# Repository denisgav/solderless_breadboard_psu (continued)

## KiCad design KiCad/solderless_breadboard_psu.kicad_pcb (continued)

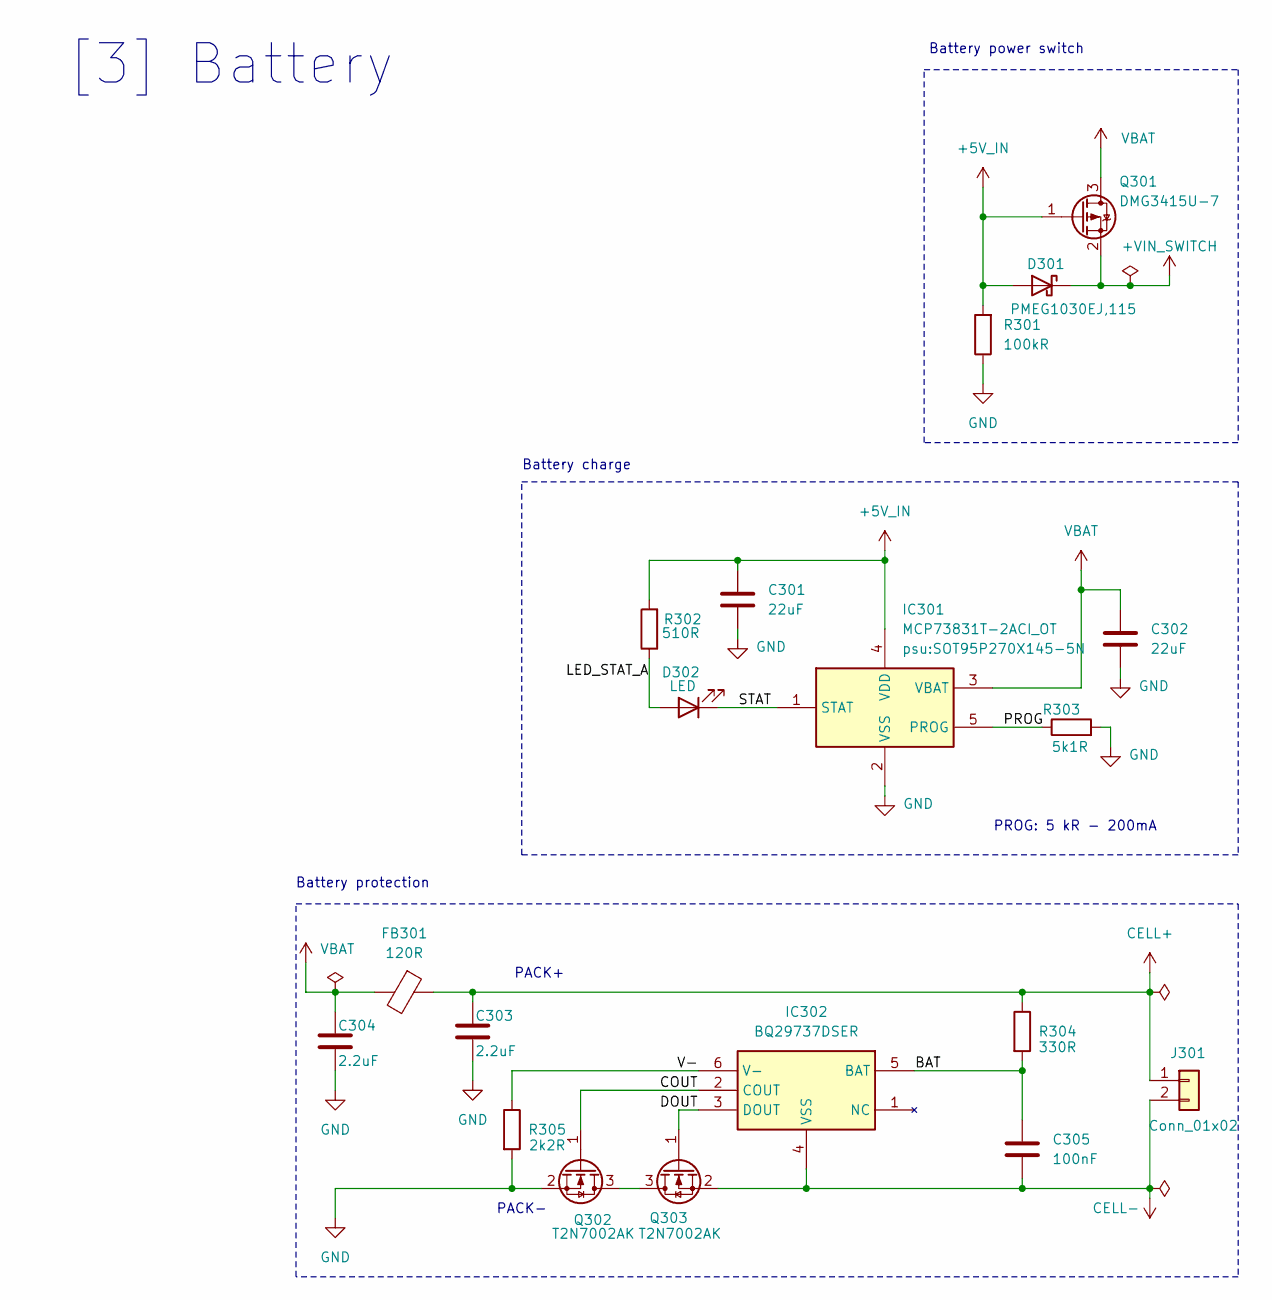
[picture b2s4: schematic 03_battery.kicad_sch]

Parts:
C301, C302: 22uF; C_0603_1608Metric; Manufacturer Part Number CL10A226MP8NUNE
C303, C304: 2.2uF; C_0603_1608Metric; Manufacturer Part Number CL10A225KO8NNNC
C305: 100nF; C_0402_1005Metric; Manufacturer Part Number CL05B104KO5NNNC
D301: PMEG1030EJ,115; D_SOD-323F; Manufacturer Part Number PMEG1030EJ,115
D302: LED; LED_0603_1608Metric; Manufacturer Part Number XL-1608SURC-06
FB301: 120R; Fuse_0603_1608Metric; Manufacturer Part Number BLM18PG121SN1D
IC301: MCP73831T-2ACI_OT; SOT95P270X145-5N; Manufacturer Part Number MCP73831T-2ACI/OT
IC302: BQ29737DSER; SON50P150X150X80-6N; Manufacturer Part Number BQ29737DSER
J301: Conn_01x02; PinHeader_1x02_P2.54mm_Vertical
Q301: DMG3415U-7; SOT-23; Manufacturer Part Number DMG3415U-7
Q302, Q303: T2N7002AK; SOT-23; Manufacturer Part Number T2N7002AK,LM
R301: 100kR; R_0402_1005Metric; Manufacturer Part Number 0402WGF1003TCE
R302: 510R; R_0402_1005Metric; Manufacturer Part Number 0402WGF5100TCE
R303: 5k1R; R_0402_1005Metric; Manufacturer Part Number 0402WGF5101TCE
R304: 330R; R_0402_1005Metric; Manufacturer Part Number 0402WGF3300TCE
R305: 2k2R; R_0402_1005Metric; Manufacturer Part Number 0402WGF2201TCE

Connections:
+5V_IN: C301.1, D301.2 (A), IC301.4 (VDD), Q301.1 (G), R301.2, R302.2; also elsewhere on the board
+VIN_SWITCH: D301.1 (K), Q301.2 (S); also elsewhere on the board
/[3] Battery/BAT: C305.1, IC302.5 (BAT), R304.2
/[3] Battery/COUT: IC302.2 (COUT), Q302.1 (G)
/[3] Battery/DOUT: IC302.3 (DOUT), Q303.1 (G)
/[3] Battery/LED_STAT_A: D302.2 (A), R302.1
/[3] Battery/PROG: IC301.5 (PROG), R303.1
/[3] Battery/STAT: D302.1 (K), IC301.1 (STAT)
/[3] Battery/V-: IC302.6 (V-), R305.1
CELL+: C303.1, FB301.1, J301.1, R304.1
CELL-: C305.2, IC302.4 (VSS), J301.2, Q303.2 (S)
GND: C301.2, C302.2, C303.2, C304.2, IC301.2 (VSS), Q302.2 (S), R301.1, R303.2, R305.2; also elsewhere on the board
unnamed: Q302.3 (D), Q303.3 (D)
VBAT: C302.1, C304.1, FB301.2, IC301.3 (VBAT), Q301.3 (D)

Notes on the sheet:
Battery charge
PACK-
Battery protection
Battery power switch
[3] Battery
PROG: 5 kR - 200mA
PACK+

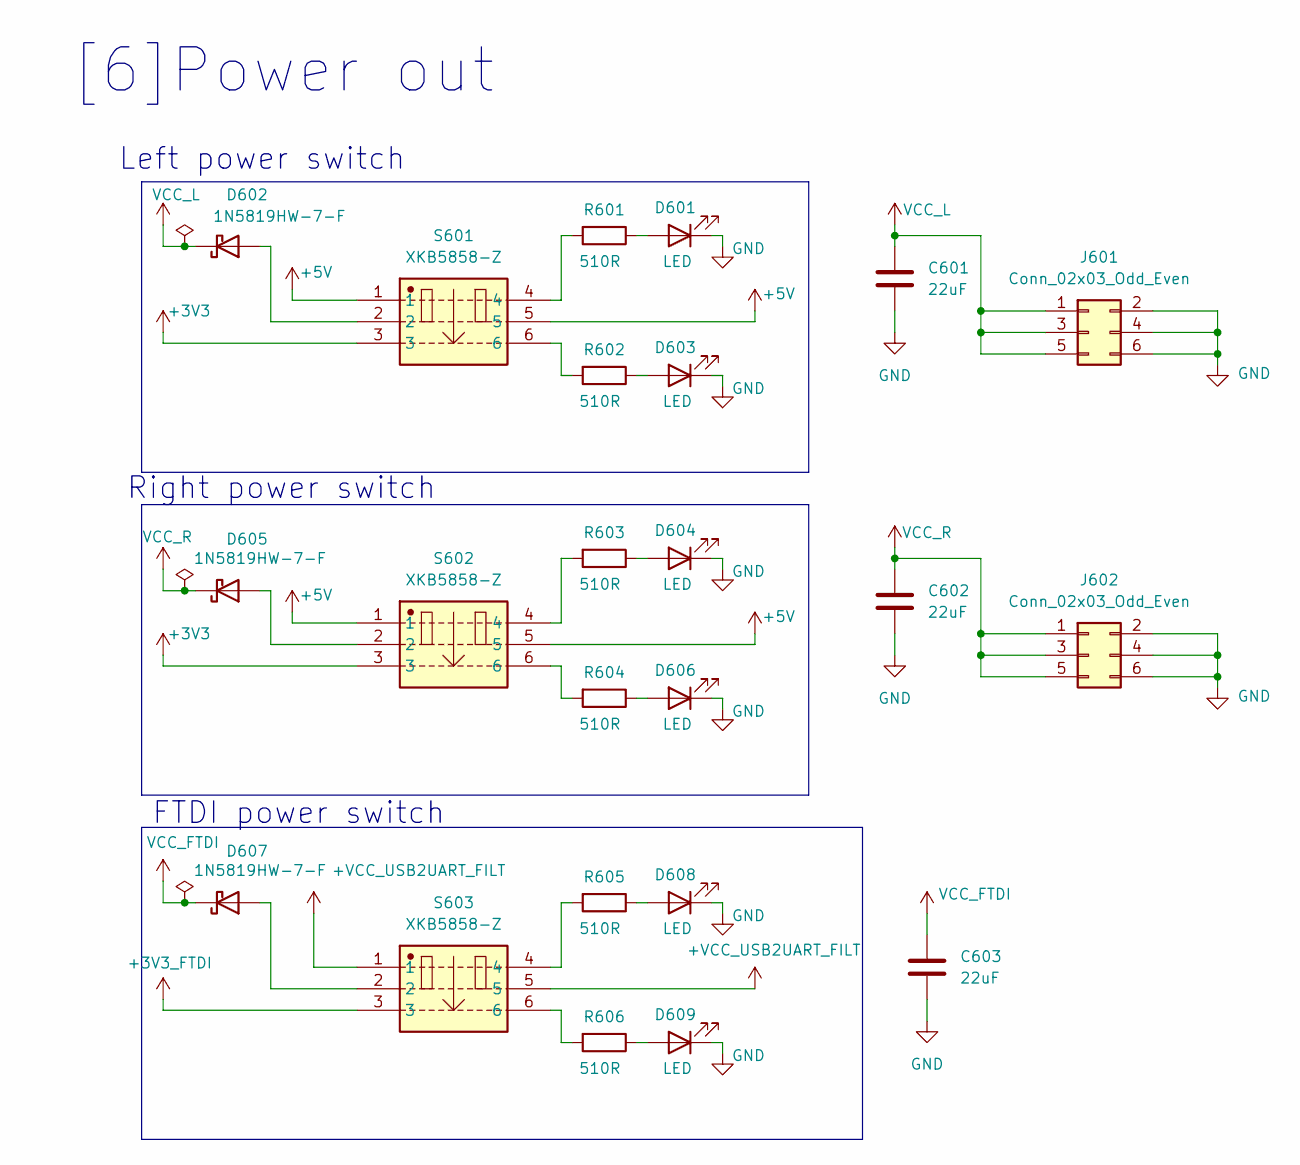
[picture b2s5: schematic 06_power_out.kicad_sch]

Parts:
C601, C602, C603: 22uF; C_0603_1608Metric; Manufacturer Part Number CL10A226MP8NUNE; DigiKey Part Number 1276-6687-6-ND
D601, D603, D604, D606, D608, D609: LED; LED_0603_1608Metric; Manufacturer Part Number XL-1608SURC-06
D602, D605, D607: 1N5819HW-7-F; D_SOD-123; Manufacturer Part Number 1N5819HW-7-F
J601, J602: Conn_02x03_Odd_Even; PinHeader_2x03_P2.54mm_Vertical
R601, R602, R603, R604, R605, R606: 510R; R_0402_1005Metric; Manufacturer Part Number 0402WGF5100TCE
S601, S602, S603: XKB5858-Z; XKB5858Z; Manufacturer Part Number XKB5858-Z

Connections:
+3V3: S601.3, S602.3; also elsewhere on the board
+3V3_FTDI: S603.3; also elsewhere on the board
+5V: S601.1, S601.5, S602.1, S602.5; also elsewhere on the board
+VCC_USB2UART_FILT: S603.1, S603.5; also elsewhere on the board
GND: C601.2, C602.2, C603.2, D601.1 (K), D603.1 (K), D604.1 (K), D606.1 (K), D608.1 (K), D609.1 (K), J601.2, J601.4, J601.6, J602.2, J602.4, J602.6; also elsewhere on the board
unnamed: D601.2 (A), R601.1
unnamed: D602.2 (A), S601.2
unnamed: D603.2 (A), R602.1
unnamed: D604.2 (A), R603.1
unnamed: D605.2 (A), S602.2
unnamed: D606.2 (A), R604.1
unnamed: D607.2 (A), S603.2
unnamed: D608.2 (A), R605.1
unnamed: D609.2 (A), R606.1
unnamed: R601.2, S601.4
unnamed: R602.2, S601.6
unnamed: R603.2, S602.4
unnamed: R604.2, S602.6
unnamed: R605.2, S603.4
unnamed: R606.2, S603.6
VCC_FTDI: C603.1, D607.1 (K); also elsewhere on the board
VCC_L: C601.1, D602.1 (K), J601.1, J601.3, J601.5
VCC_R: C602.1, D605.1 (K), J602.1, J602.3, J602.5

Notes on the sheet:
FTDI power switch
Left power switch
Right power switch
[6]Power out

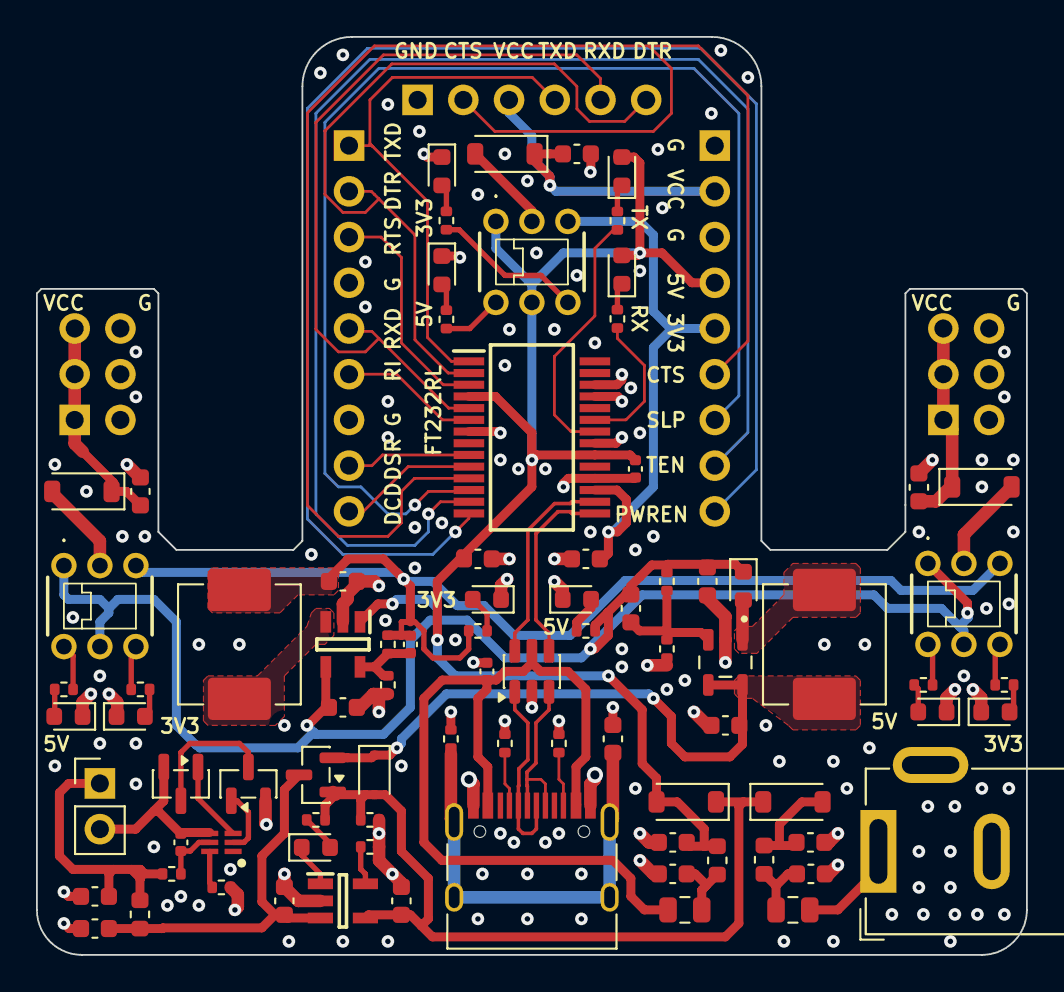
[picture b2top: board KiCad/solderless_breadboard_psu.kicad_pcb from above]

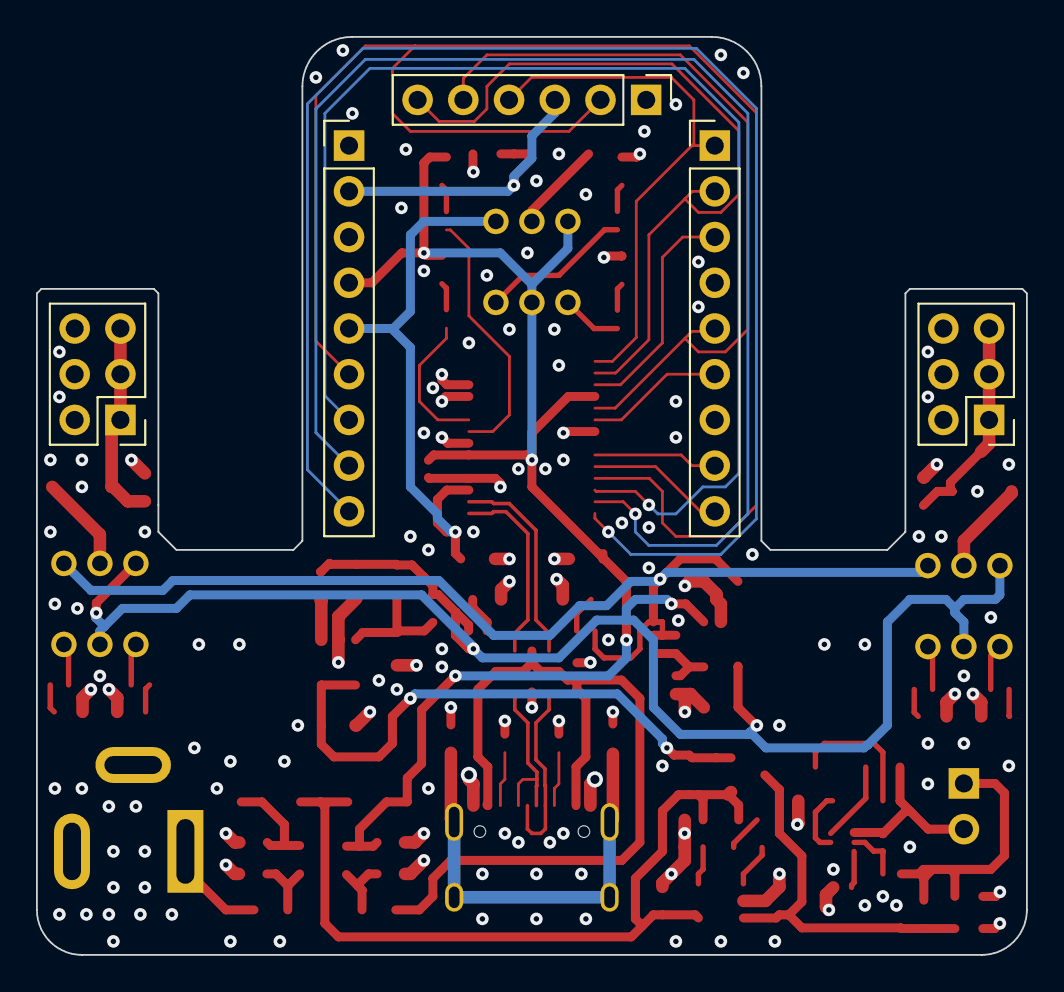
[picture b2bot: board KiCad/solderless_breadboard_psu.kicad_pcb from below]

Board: 4 copper layers, 55.0 x 51.0 mm, 90 parts (5 on the bottom side), 69 nets.

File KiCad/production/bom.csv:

Designator,Footprint,Quantity,Value,LCSC Part #
"C201, C202, C203, C204, C303, C304",0603,6,2.2uF,
"C301, C302, C401, C402, C404, C406, C501, C503, C601, C602, C603",0603,11,22uF,
"C305, C502, C504",0402,3,100nF,
C403,0402,1,DNP,
C405,0603,1,30pF,
C505,0603,1,1nF,
"D201, D202",D_SOD-123,2,1N5819HW-7-F,
D301,D_SOD-323F,1,"PMEG1030EJ,115",
"D302, D402, D403, D501, D502, D601, D602, D603, D604, D605, D606",0603,11,LED,
D401,D_SMA,1,SS14,
"F201, F202",0805,2,3A,
"FB201, FB202, FB301",0603,3,120R,
IC301,SOT95P270X145-5N,1,MCP73831T-2ACI_OT,
IC302,SON50P150X150X80-6N,1,BQ29737DSER,
IC401,SOT95P280X145-5N,1,TLV62569DBVR,
IC501,SOP65P778X200-28N,1,FT232RL-REEL,
J201,BarrelJack_GCT_DCJ200-10-A_Horizontal,1,Barrel_Jack_Switch_Pin3Ring,
J301,BM02B-GHS-TBT_1,1,BM02B-GHS-TBT_LF__SN__N_,
"J501, J502",PinHeader_1x09_P2.54mm_Vertical,2,Conn_01x09_Pin,
J503,PinHeader_1x06_P2.54mm_Vertical,1,Conn_01x06_Pin,
J504,USB_C_Receptacle_HRO_TYPE-C-31-M-12,1,USB_C_Receptacle_USB2.0_16P,
"J601, J602",PinHeader_2x03_P2.54mm_Vertical,2,Conn_02x03_Odd_Even,
L401,L_Changjiang_FXL0630,1,10uH,
L402,L_Changjiang_FXL0630,1,15uH,
Q301,SOT-23,1,DMG3415U-7,
"Q302, Q303",SOT-23,2,T2N7002AK,
"R301, R401",0402,2,100kR,
"R302, R405, R406, R503, R504, R601, R602, R603, R604, R605, R606",0402,11,510R,
"R303, R501, R502",0402,3,5k1R,
R304,0402,1,330R,
R305,0402,1,2k2R,
"R402, R505",0402,2,1MR,
R403,0402,1,22kR,
R404,0402,1,330kR,
"S601, S602, S603",XKB5858Z,3,XKB5858-Z,
U401,TPS61040DBVR,1,TPS61040DBVR,
U501,SOT-23-6,1,USBLC6-2SC6,

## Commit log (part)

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2026-01-10 First scheme complete
2026-01-10 Add power out capacitors
2026-01-11 ERC fixes
2026-01-11 basic PCB
2026-01-11 minor pcb update
2026-01-11 Calculated pin headers positions
2026-01-13 minor PCB updates
2026-01-15 Add board edge cuts
2026-01-17 Update FTDI pin header
2026-01-17 USB routing
2026-01-17 PCB UART routing
2026-01-17 Update FTDI pinout
2026-01-18 FTDI signals routing
2026-01-18 battery connector PCB routing
2026-01-18 PCB route complete
2026-01-18 PCB DRC fixes
2026-01-24 Fill BOM table
2026-01-24 Production files
2026-01-24 battery connector update
2026-01-25 Update battery connector
2026-01-25 Update pin header offset. Clean DRC error
2026-01-25 JLCPCB check fixes
2026-02-28 BOM updates
2026-03-15 Update resistor values
2026-05-03 Add V2 folder
2026-05-03 USB2UART scheme update
2026-05-04 scheme for voltage regulators
2026-05-05 Update USB connection scheme
2026-05-06 Scheme updates
2026-05-06 update FB capacitors
2026-05-07 Initial components placement
2026-05-08 PCB layout updates
2026-05-09 board outline fix
2026-05-09 initial routing
2026-05-09 power signals routing
2026-05-10 Signal routing
2026-05-10 First routing
2026-05-11 silkscreen updates
